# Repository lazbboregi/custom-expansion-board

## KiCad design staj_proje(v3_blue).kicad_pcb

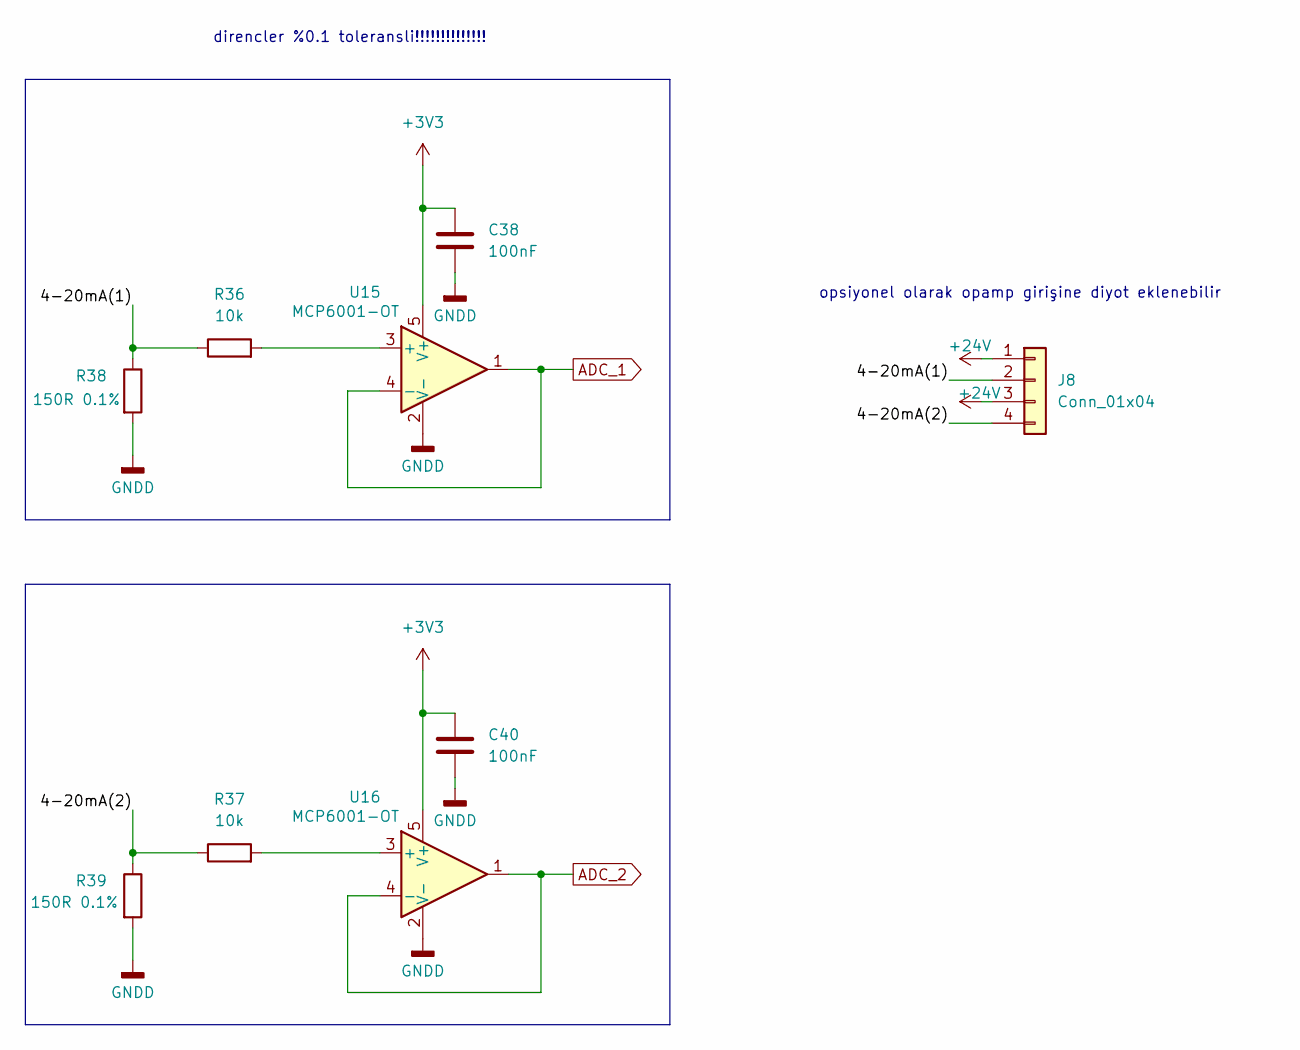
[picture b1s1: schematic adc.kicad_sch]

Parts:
C38, C40: 100nF; C_0805_2012Metric
J8: Conn_01x04; PhoenixContact_MC_1,5_4-G-3.81_1x04_P3.81mm_Horizontal
R36, R37: 10k; R_0805_2012Metric
R38, R39: 150R 0.1%; R_0805_2012Metric
U15, U16: MCP6001-OT; SOT-23-5

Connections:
+3V3: C38.1, C40.1, U15.5 (V+), U16.5 (V+); also elsewhere on the board
+24V: J8.1, J8.3; also elsewhere on the board
/ADC/4-20mA(1): J8.2, R36.1, R38.1
/ADC/4-20mA(2): J8.4, R37.1, R39.1
ADC_1: U15.1, U15.4 (-); also elsewhere on the board
ADC_2: U16.1, U16.4 (-); also elsewhere on the board
GNDD: C38.2, C40.2, R38.2, R39.2, U15.2 (V-), U16.2 (V-); also elsewhere on the board
unnamed: R36.2, U15.3 (+)
unnamed: R37.2, U16.3 (+)

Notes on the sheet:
direncler %0.1 toleransli!!!!!!!!!!!!!!
opsiyonel olarak opamp girişine diyot eklenebilir

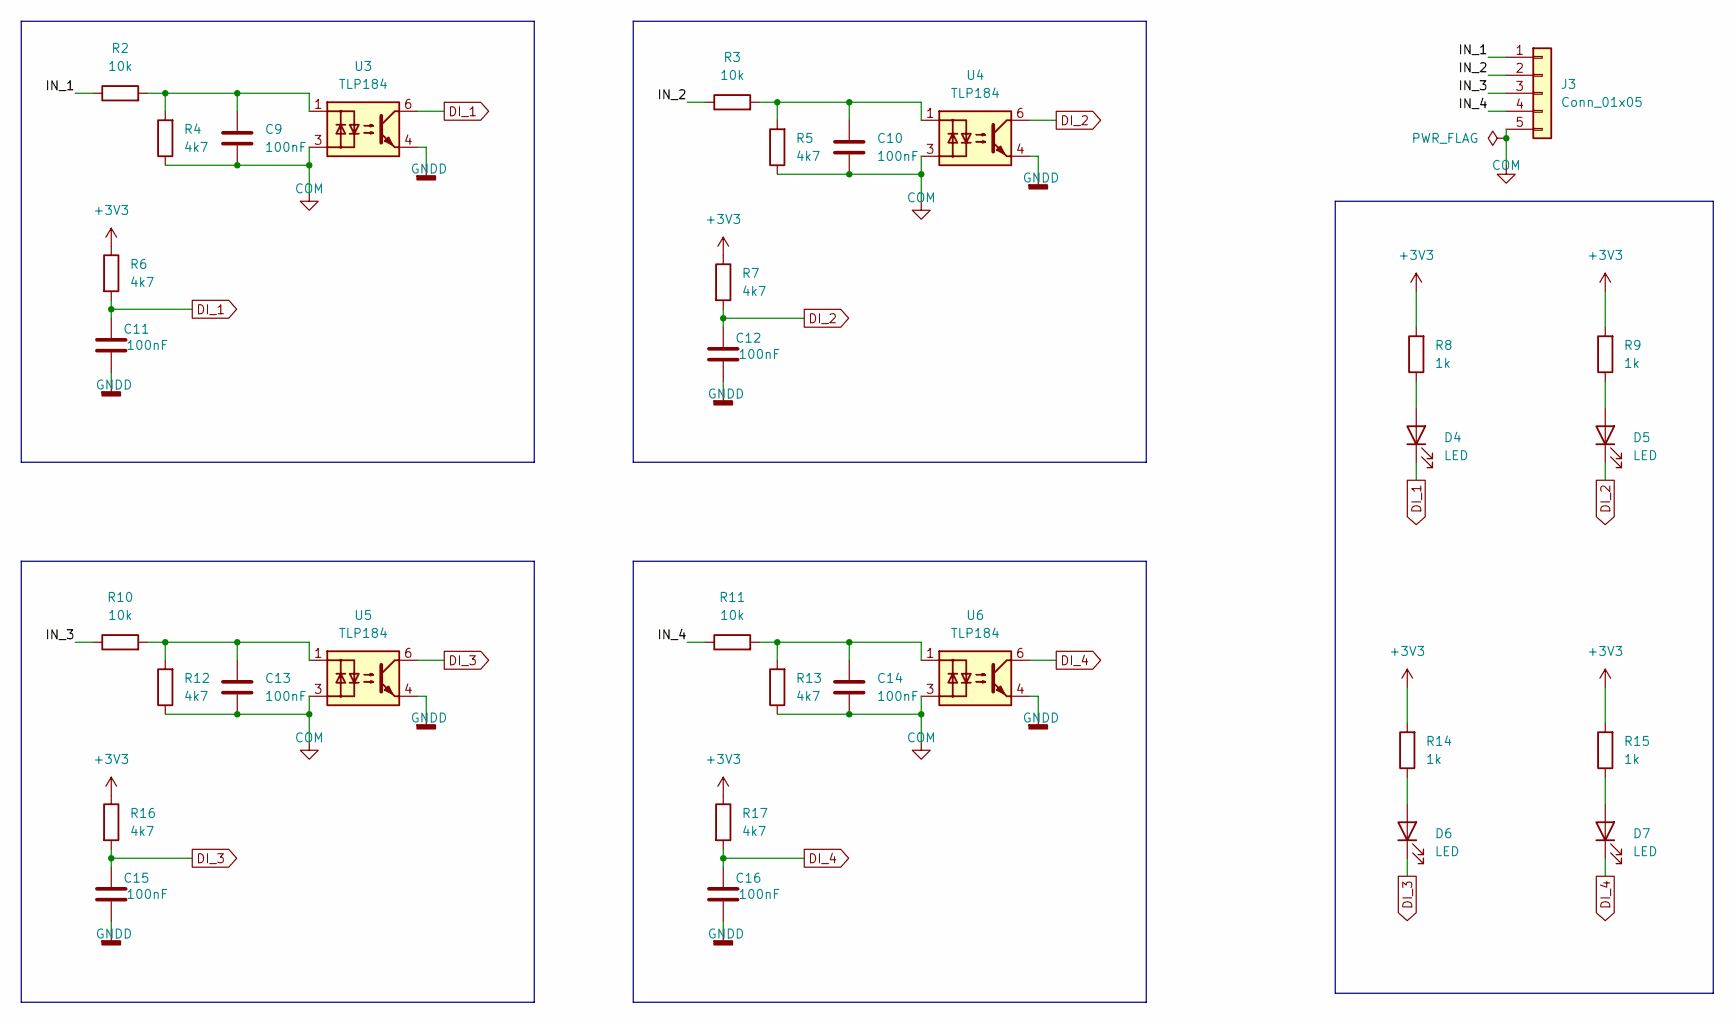
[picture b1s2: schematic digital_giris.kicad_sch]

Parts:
C9, C10, C11, C12, C13, C14, C15, C16: 100nF; C_0805_2012Metric
D4, D5, D6, D7: LED; LED_0603_1608Metric
J3: Conn_01x05; PhoenixContact_MC_1,5_5-G-3.81_1x05_P3.81mm_Horizontal
R2, R3, R10, R11: 10k; R_0805_2012Metric
R4, R5, R6, R7, R12, R13, R16, R17: 4k7; R_0805_2012Metric
R8, R9, R14, R15: 1k; R_0805_2012Metric
U3, U4, U5, U6: TLP184; Toshiba_SOIC-4-6_4.4x3.6mm_P1.27mm

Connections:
+3V3: R6.1, R7.1, R8.2, R9.2, R14.2, R15.2, R16.1, R17.1; also elsewhere on the board
/4x izole digital giris/IN_1: J3.1, R2.1
/4x izole digital giris/IN_2: J3.2, R3.1
/4x izole digital giris/IN_3: J3.3, R10.1
/4x izole digital giris/IN_4: J3.4, R11.1
COM: C9.1, C10.1, C13.1, C14.1, J3.5, R4.1, R5.1, R12.1, R13.1, U3.3, U4.3, U5.3, U6.3
DI_1: C11.1, D4.1 (K), R6.2, U3.6; also elsewhere on the board
DI_2: C12.1, D5.1 (K), R7.2, U4.6; also elsewhere on the board
DI_3: C15.1, D6.1 (K), R16.2, U5.6; also elsewhere on the board
DI_4: C16.1, D7.1 (K), R17.2, U6.6; also elsewhere on the board
GNDD: C11.2, C12.2, C15.2, C16.2, U3.4, U4.4, U5.4, U6.4; also elsewhere on the board
unnamed: C9.2, R2.2, R4.2, U3.1
unnamed: C10.2, R3.2, R5.2, U4.1
unnamed: C13.2, R10.2, R12.2, U5.1
unnamed: C14.2, R11.2, R13.2, U6.1
unnamed: D4.2 (A), R8.1
unnamed: D5.2 (A), R9.1
unnamed: D6.2 (A), R14.1
unnamed: D7.2 (A), R15.1

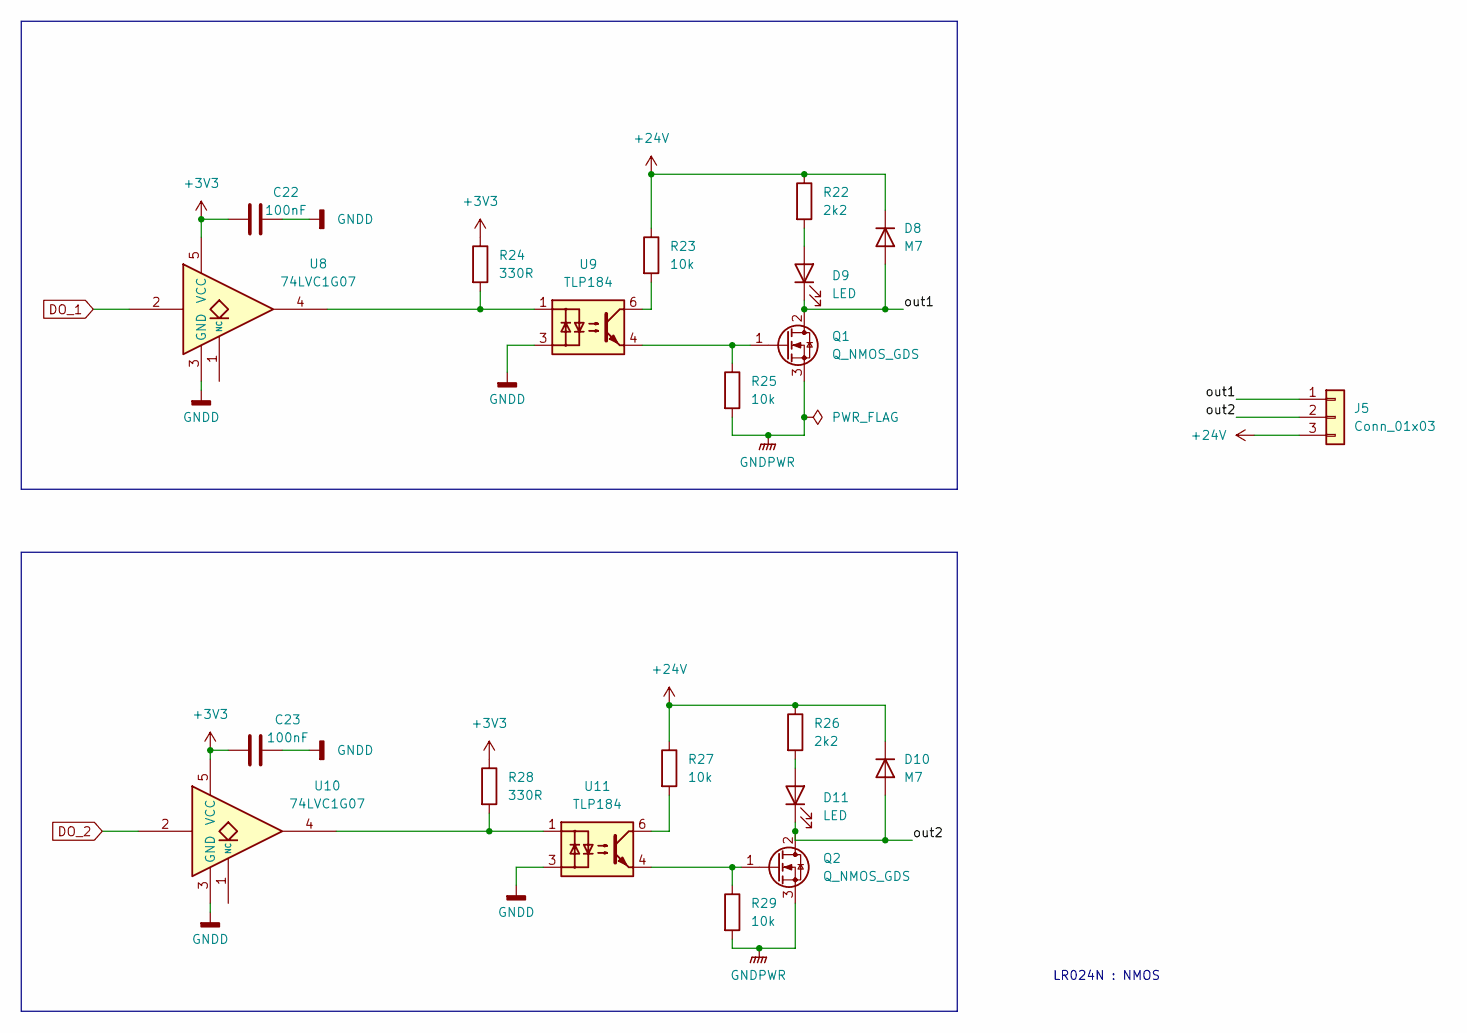
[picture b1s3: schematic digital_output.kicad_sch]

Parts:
C22, C23: 100nF; C_0805_2012Metric
D8, D10: M7; D_SMA
D9, D11: LED; LED_0603_1608Metric
J5: Conn_01x03; PhoenixContact_MC_1,5_3-G-3.81_1x03_P3.81mm_Horizontal
Q1, Q2: Q_NMOS_GDS; TO-252-3_TabPin2
R22, R26: 2k2; R_0805_2012Metric
R23, R25, R27, R29: 10k; R_0805_2012Metric
R24, R28: 330R; R_0805_2012Metric
U8, U10: 74LVC1G07; SOT-23-5
U9, U11: TLP184; Toshiba_SOIC-4-6_4.4x3.6mm_P1.27mm

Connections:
+3V3: C22.2, C23.2, R24.1, R28.1, U8.5 (VCC), U10.5 (VCC); also elsewhere on the board
+24V: D8.1 (K), D10.1 (K), J5.3, R22.1, R23.1, R26.1, R27.1; also elsewhere on the board
/2x digital output/out1: D8.2 (A), D9.1 (K), J5.1, Q1.2 (D)
/2x digital output/out2: D10.2 (A), D11.1 (K), J5.2, Q2.2 (D)
DO_1: U8.2; also elsewhere on the board
DO_2: U10.2; also elsewhere on the board
GNDD: C22.1, C23.1, U8.3 (GND), U9.3, U10.3 (GND), U11.3; also elsewhere on the board
GNDPWR: Q1.3 (S), Q2.3 (S), R25.2, R29.2
unnamed: D9.2 (A), R22.2
unnamed: D11.2 (A), R26.2
unnamed: Q1.1 (G), R25.1, U9.4
unnamed: Q2.1 (G), R29.1, U11.4
unnamed: R23.2, U9.6
unnamed: R24.2, U8.4, U9.1
unnamed: R27.2, U11.6
unnamed: R28.2, U10.4, U11.1

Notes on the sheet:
LR024N : NMOS

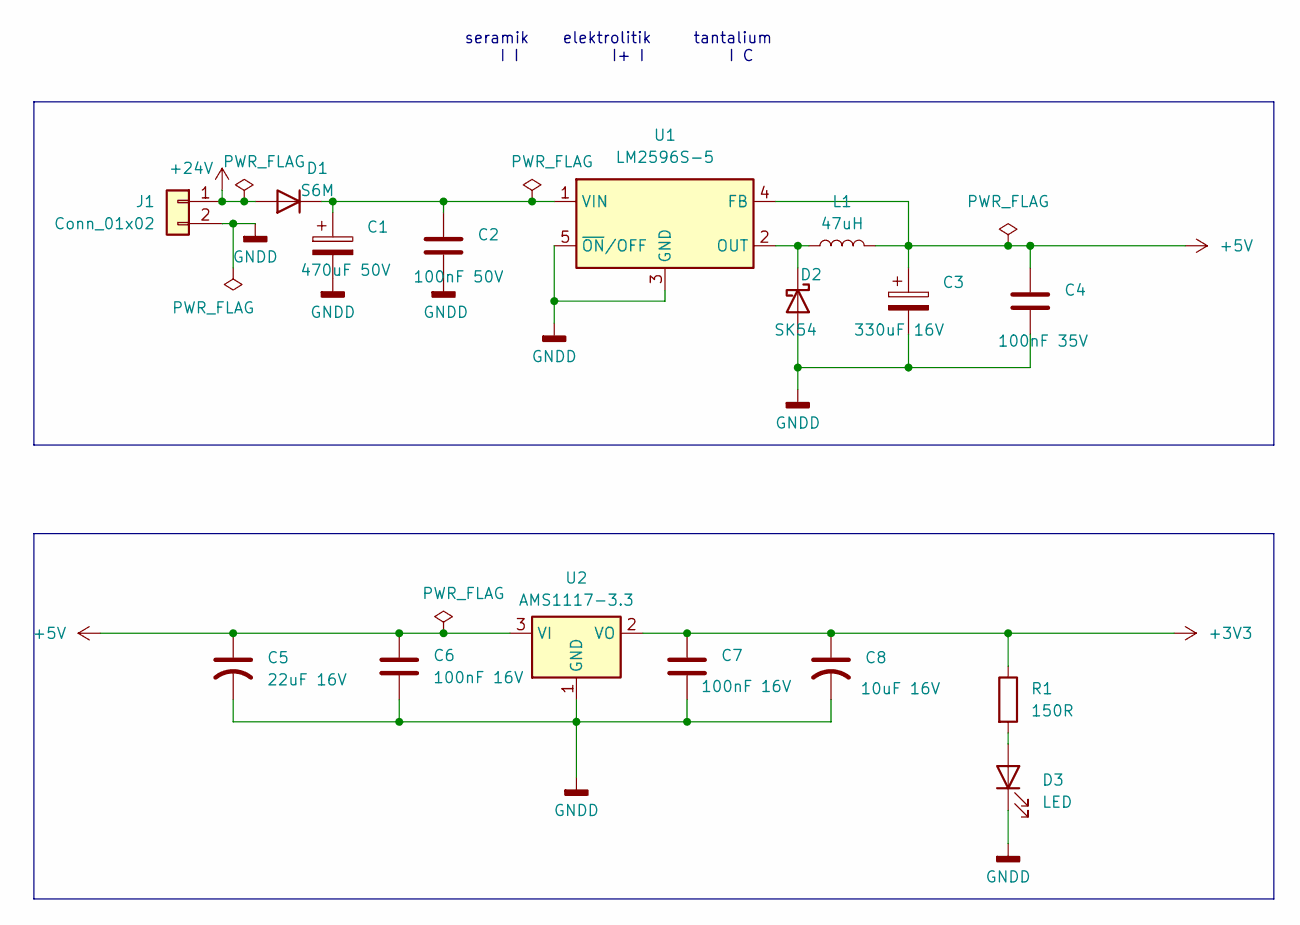
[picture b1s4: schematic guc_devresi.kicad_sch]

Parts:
C1: 470uF 50V; CP_Elec_8x10
C2: 100nF 50V; C_0805_2012Metric
C3: 330uF 16V; CP_Elec_8x10
C4: 100nF 35V; C_0805_2012Metric
C5: 22uF 16V; CP_EIA-3528-21_Kemet-B
C6, C7: 100nF 16V; C_0805_2012Metric
C8: 10uF 16V; CP_EIA-3528-21_Kemet-B
D1: S6M; D_SMC
D2: SK54; ST_D_SMC
D3: LED; LED_0603_1608Metric
J1: Conn_01x02; PhoenixContact_MC_1,5_2-G-3.81_1x02_P3.81mm_Horizontal
L1: 47uH; WE-PD_1210
R1: 150R; R_0805_2012Metric
U1: LM2596S-5; TO-263-5_TabPin3
U2: AMS1117-3.3; SOT-223-3_TabPin2

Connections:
+3V3: C7.1, C8.1, R1.1, U2.2 (VO); also elsewhere on the board
+5V: C3.1, C4.1, C5.1, C6.1, L1.2, U1.4 (FB), U2.3 (VI); also elsewhere on the board
+24V: D1.2 (A), J1.1; also elsewhere on the board
GNDD: C1.2, C2.2, C3.2, C4.2, C5.2, C6.2, C7.2, C8.2, D2.2 (A), D3.1 (K), J1.2, U1.3 (GND), U1.5 (~ON/OFF), U2.1 (GND); also elsewhere on the board
unnamed: C1.1, C2.1, D1.1 (K), U1.1 (VIN)
unnamed: D2.1 (K), L1.1, U1.2 (OUT)
unnamed: D3.2 (A), R1.2

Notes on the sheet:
seramik elektrolitik tantalium I I I+ I I C

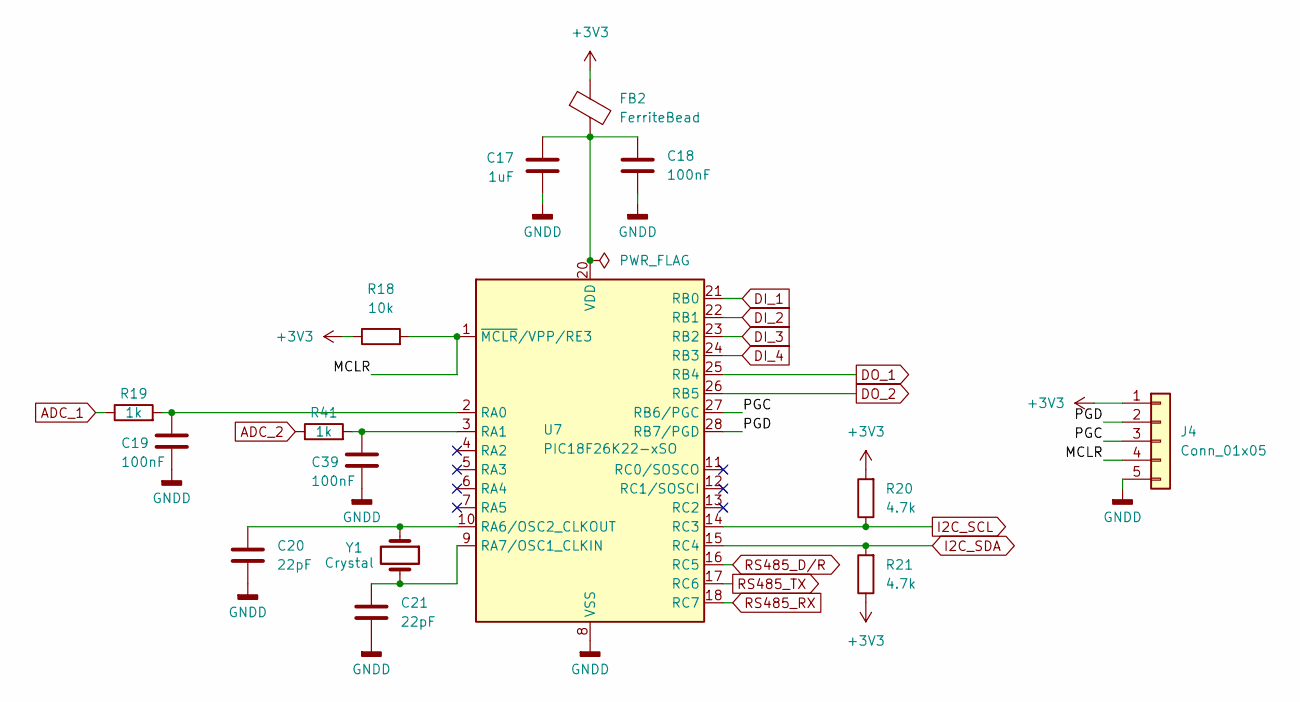
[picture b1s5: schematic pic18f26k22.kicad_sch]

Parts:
C17: 1uF; C_0805_2012Metric
C18, C19, C39: 100nF; C_0805_2012Metric
C20, C21: 22pF; C_0805_2012Metric
FB2: FerriteBead; L_0805_2012Metric
J4: Conn_01x05; PinHeader_1x05_P2.54mm_Vertical
R18: 10k; R_0805_2012Metric
R19, R41: 1k; R_0805_2012Metric
R20, R21: 4.7k; R_0805_2012Metric
U7: PIC18F26K22-xSO; SOIC-28W_7.5x17.9mm_P1.27mm
Y1: Crystal; Crystal_SMD_HC49-SD

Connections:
+3V3: FB2.1, J4.1, R18.1, R20.2, R21.1; also elsewhere on the board
/MCU/MCLR: J4.4, R18.2, U7.1 (~MCLR/VPP/RE3)
/MCU/PGC: J4.3, U7.27 (RB6/PGC)
/MCU/PGD: J4.2, U7.28 (RB7/PGD)
ADC_1: R19.1; also elsewhere on the board
ADC_2: R41.1; also elsewhere on the board
DI_1: U7.21 (RB0); also elsewhere on the board
DI_2: U7.22 (RB1); also elsewhere on the board
DI_3: U7.23 (RB2); also elsewhere on the board
DI_4: U7.24 (RB3); also elsewhere on the board
DO_1: U7.25 (RB4); also elsewhere on the board
DO_2: U7.26 (RB5); also elsewhere on the board
GNDD: C17.1, C18.2, C19.2, C20.2, C21.2, C39.2, J4.5, U7.8 (VSS), U7.19 (VSS); also elsewhere on the board
I2C_SCL: R20.1, U7.14 (RC3); also elsewhere on the board
I2C_SDA: R21.2, U7.15 (RC4); also elsewhere on the board
unnamed: C19.1, R19.2, U7.2 (RA0)
unnamed: C39.1, R41.2, U7.3 (RA1)
unnamed: C20.1, U7.10 (RA6/OSC2_CLKOUT), Y1.1
unnamed: C21.1, U7.9 (RA7/OSC1_CLKIN), Y1.2
unnamed: C17.2, C18.1, FB2.2, U7.20 (VDD)
RS485_D/R: U7.16 (RC5); also elsewhere on the board
RS485_RX: U7.18 (RC7); also elsewhere on the board
RS485_TX: U7.17 (RC6); also elsewhere on the board

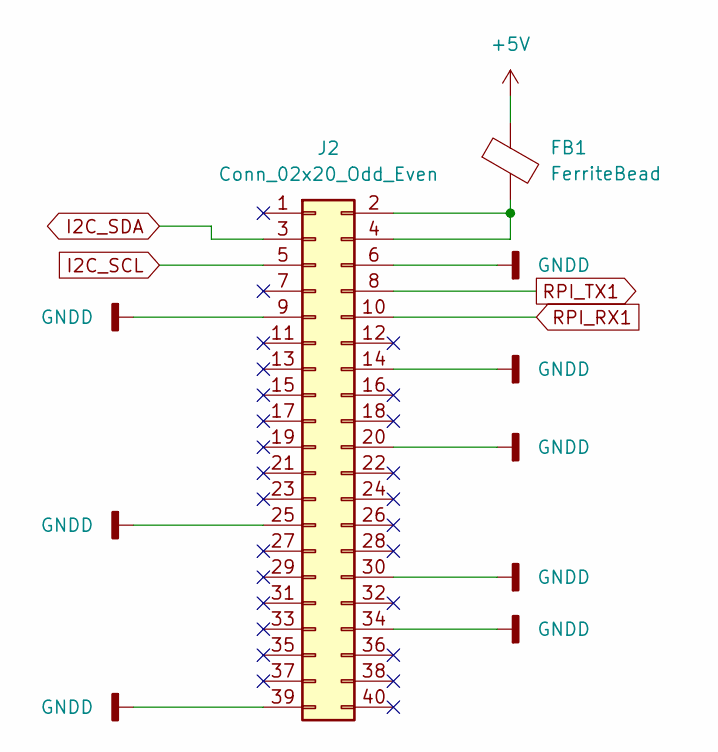
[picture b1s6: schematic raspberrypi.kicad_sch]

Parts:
FB1: FerriteBead; L_0805_2012Metric
J2: Conn_02x20_Odd_Even; RaspberryPİ4

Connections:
+5V: FB1.1; also elsewhere on the board
GNDD: J2.6, J2.9, J2.14, J2.20, J2.25, J2.30, J2.34, J2.39; also elsewhere on the board
I2C_SCL: J2.5; also elsewhere on the board
I2C_SDA: J2.3; also elsewhere on the board
unnamed: FB1.2, J2.2, J2.4
RPI_RX1: J2.10; also elsewhere on the board
RPI_TX1: J2.8; also elsewhere on the board

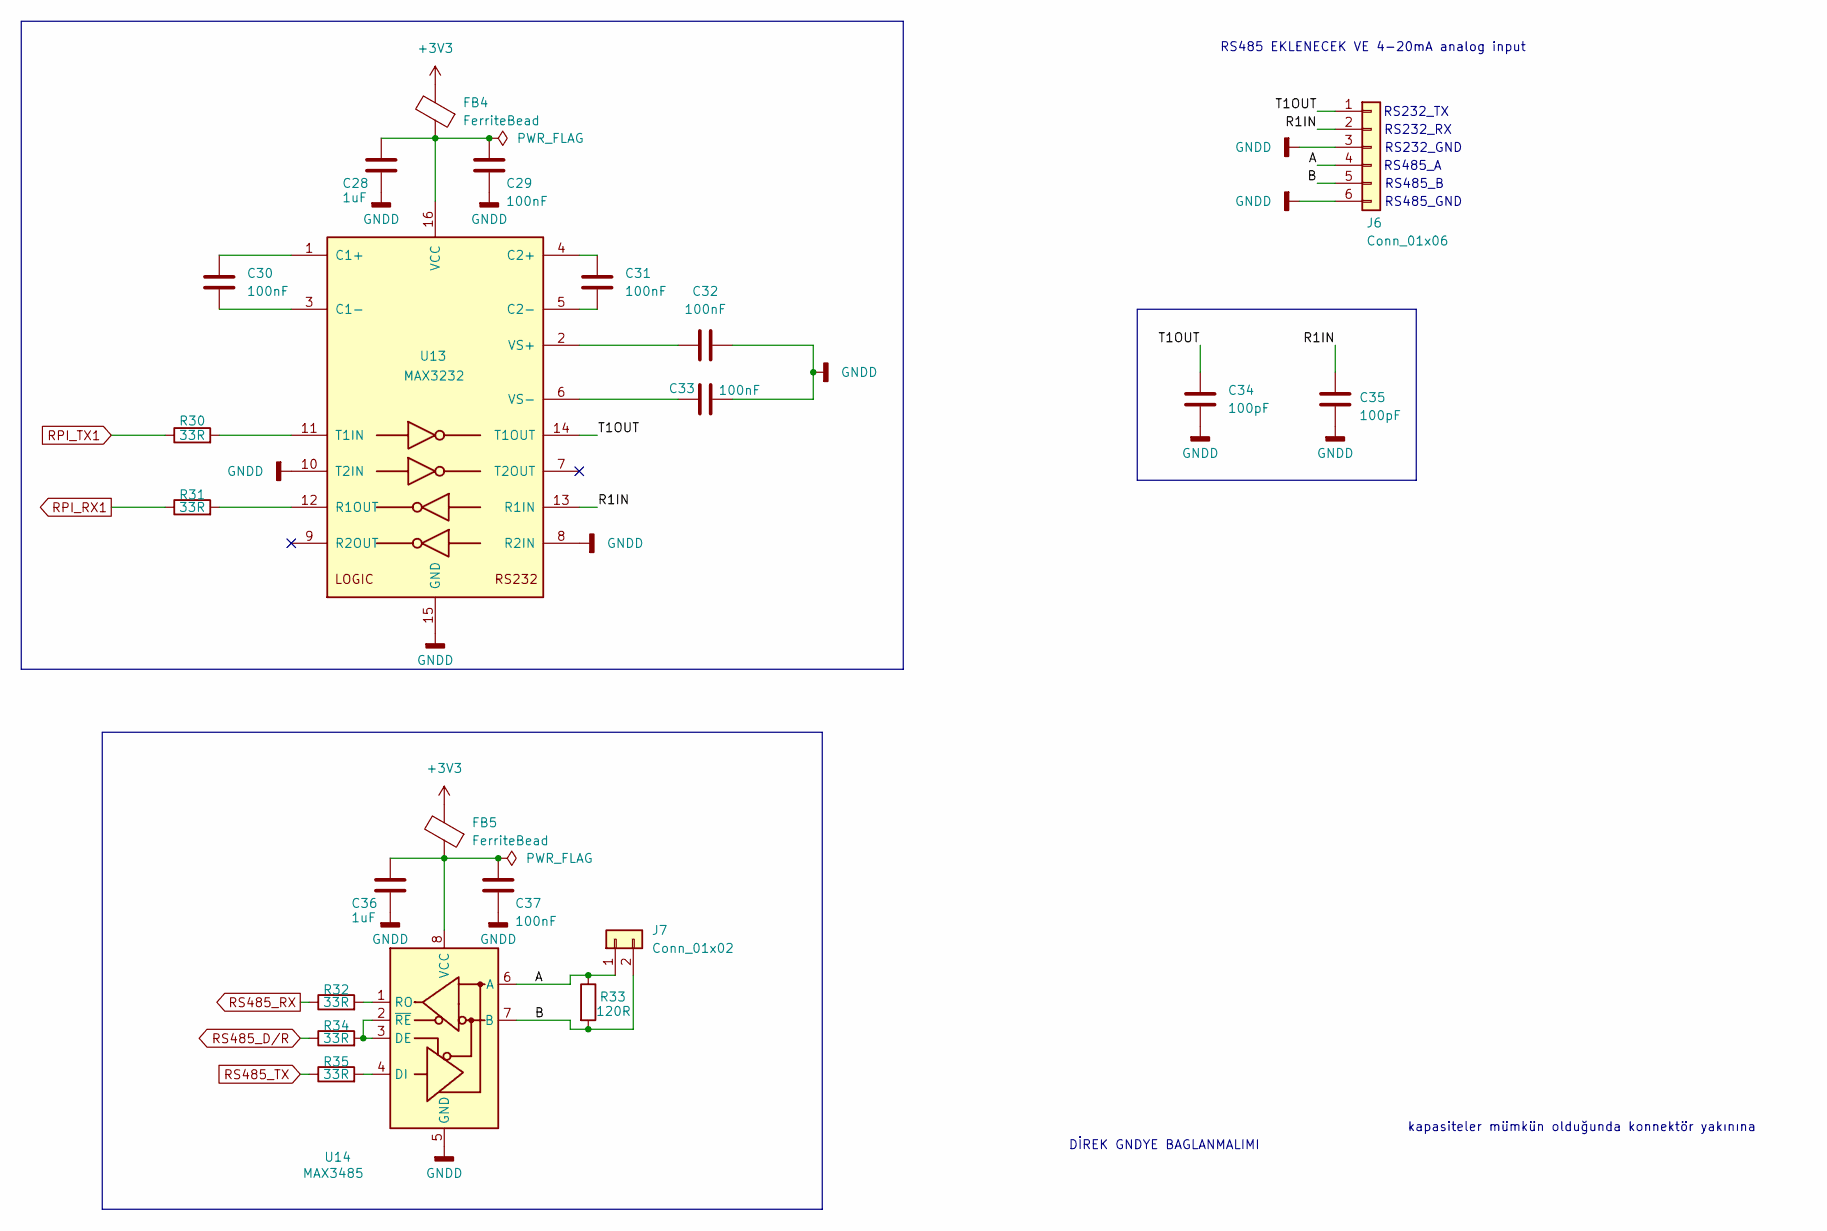
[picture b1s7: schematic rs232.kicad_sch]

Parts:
C28, C36: 1uF; C_0805_2012Metric
C29, C30, C31, C32, C33, C37: 100nF; C_0805_2012Metric
C34, C35: 100pF; C_0805_2012Metric
FB4, FB5: FerriteBead; L_0805_2012Metric
J6: Conn_01x06; PhoenixContact_MC_1,5_6-G-3.81_1x06_P3.81mm_Horizontal
J7: Conn_01x02; PinHeader_1x02_P2.54mm_Vertical
R30, R31, R32, R34, R35: 33R; R_0805_2012Metric
R33: 120R; R_0805_2012Metric
U13: MAX3232; SOIC-16_3.9x9.9mm_P1.27mm
U14: MAX3485; SOIC-8_3.9x4.9mm_P1.27mm

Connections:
+3V3: FB4.2, FB5.2; also elsewhere on the board
/rs232 COM portu/A: J6.4, J7.1, R33.1, U14.6 (A)
/rs232 COM portu/B: J6.5, J7.2, R33.2, U14.7 (B)
/rs232 COM portu/R1IN: C35.1, J6.2, U13.13 (R1IN)
/rs232 COM portu/T1OUT: C34.1, J6.1, U13.14 (T1OUT)
GNDD: C28.1, C29.2, C32.2, C33.2, C34.2, C35.2, C36.1, C37.2, J6.3, J6.6, U13.8 (R2IN), U13.10 (T2IN), U13.15 (GND), U14.5 (GND); also elsewhere on the board
unnamed: C30.1, U13.1 (C1+)
unnamed: C30.2, U13.3 (C1-)
unnamed: C31.1, U13.4 (C2+)
unnamed: C31.2, U13.5 (C2-)
unnamed: R31.2, U13.12 (R1OUT)
unnamed: R30.2, U13.11 (T1IN)
unnamed: C28.2, C29.1, FB4.1, U13.16 (VCC)
unnamed: C32.1, U13.2 (VS+)
unnamed: C33.1, U13.6 (VS-)
unnamed: R34.2, U14.2 (~RE), U14.3 (DE)
unnamed: R35.2, U14.4 (DI)
unnamed: R32.2, U14.1 (RO)
unnamed: C36.2, C37.1, FB5.1, U14.8 (VCC)
RPI_RX1: R31.1; also elsewhere on the board
RPI_TX1: R30.1; also elsewhere on the board
RS485_D/R: R34.1; also elsewhere on the board
RS485_RX: R32.1; also elsewhere on the board
RS485_TX: R35.1; also elsewhere on the board

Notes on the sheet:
RS485_B
DİREK GNDYE BAGLANMALIMI
RS485_A
kapasiteler mümkün olduğunda konnektör yakınına
RS232_GND
RS232_RX
RS232_TX
RS485_GND
RS485 EKLENECEK VE 4-20mA analog input

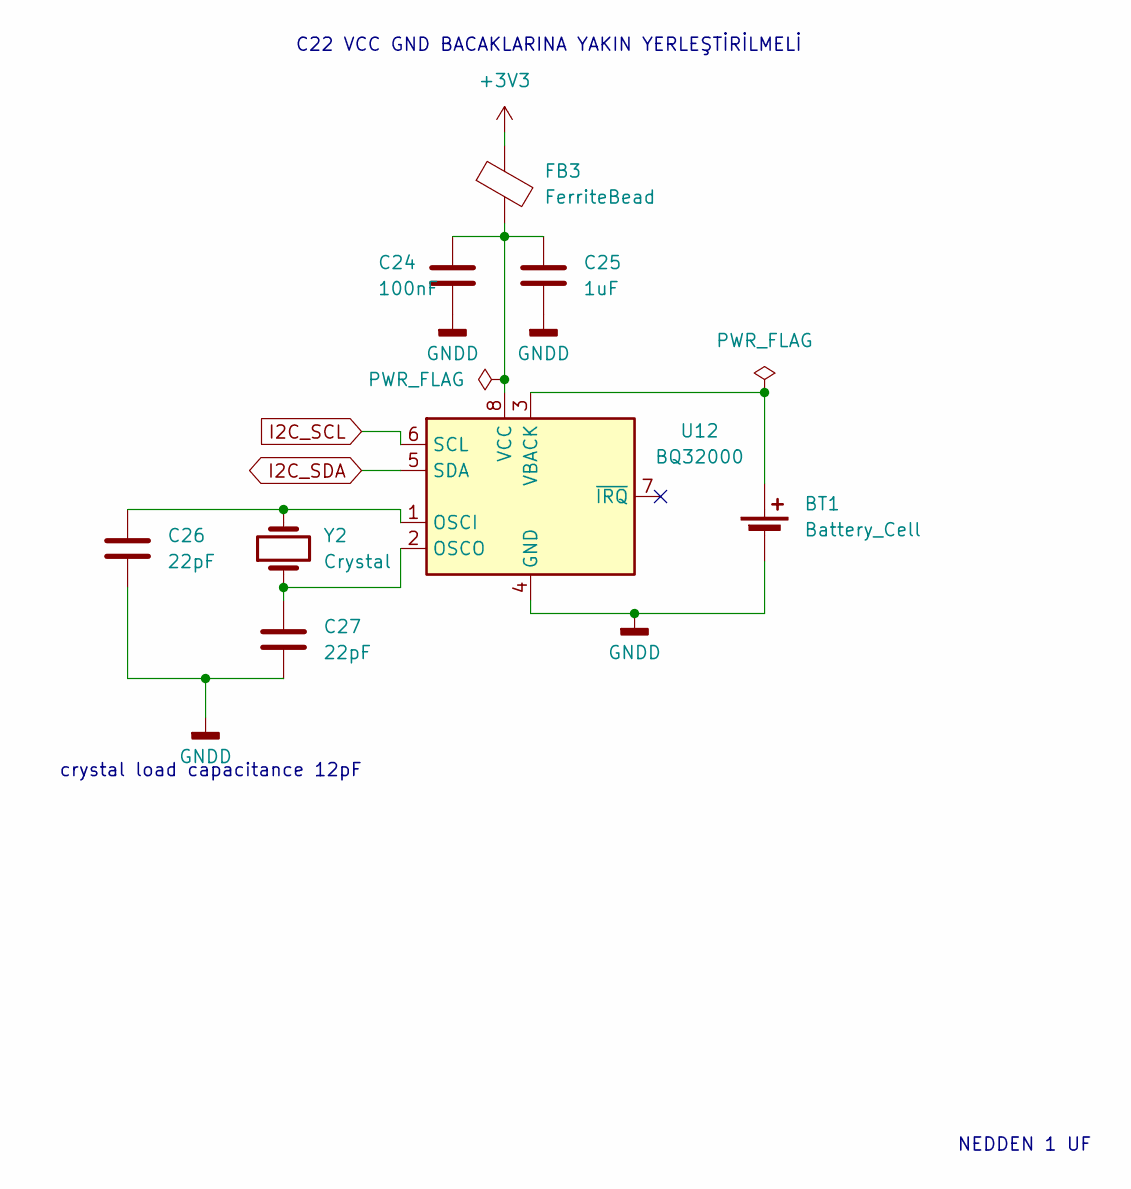
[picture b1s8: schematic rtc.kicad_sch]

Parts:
BT1: Battery_Cell; BatteryHolder_CR2032
C24: 100nF; C_0805_2012Metric
C25: 1uF; C_0805_2012Metric
C26, C27: 22pF; C_0805_2012Metric
FB3: FerriteBead; L_0805_2012Metric
U12: BQ32000; SOIC-8_3.9x4.9mm_P1.27mm
Y2: Crystal; Crystal_Round_D3.0mm_Vertical

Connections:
+3V3: FB3.1; also elsewhere on the board
GNDD: BT1.2 (-), C24.2, C25.1, C26.1, C27.1, U12.4 (GND); also elsewhere on the board
I2C_SCL: U12.6 (SCL); also elsewhere on the board
I2C_SDA: U12.5 (SDA); also elsewhere on the board
unnamed: BT1.1 (+), U12.3 (VBACK)
unnamed: C26.2, U12.1 (OSCI), Y2.2
unnamed: C27.2, U12.2 (OSCO), Y2.1
unnamed: C24.1, C25.2, FB3.2, U12.8 (VCC)

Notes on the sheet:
crystal load capacitance 12pF
C22 VCC GND BACAKLARINA YAKIN YERLEŞTİRİLMELİ
NEDDEN 1 UF

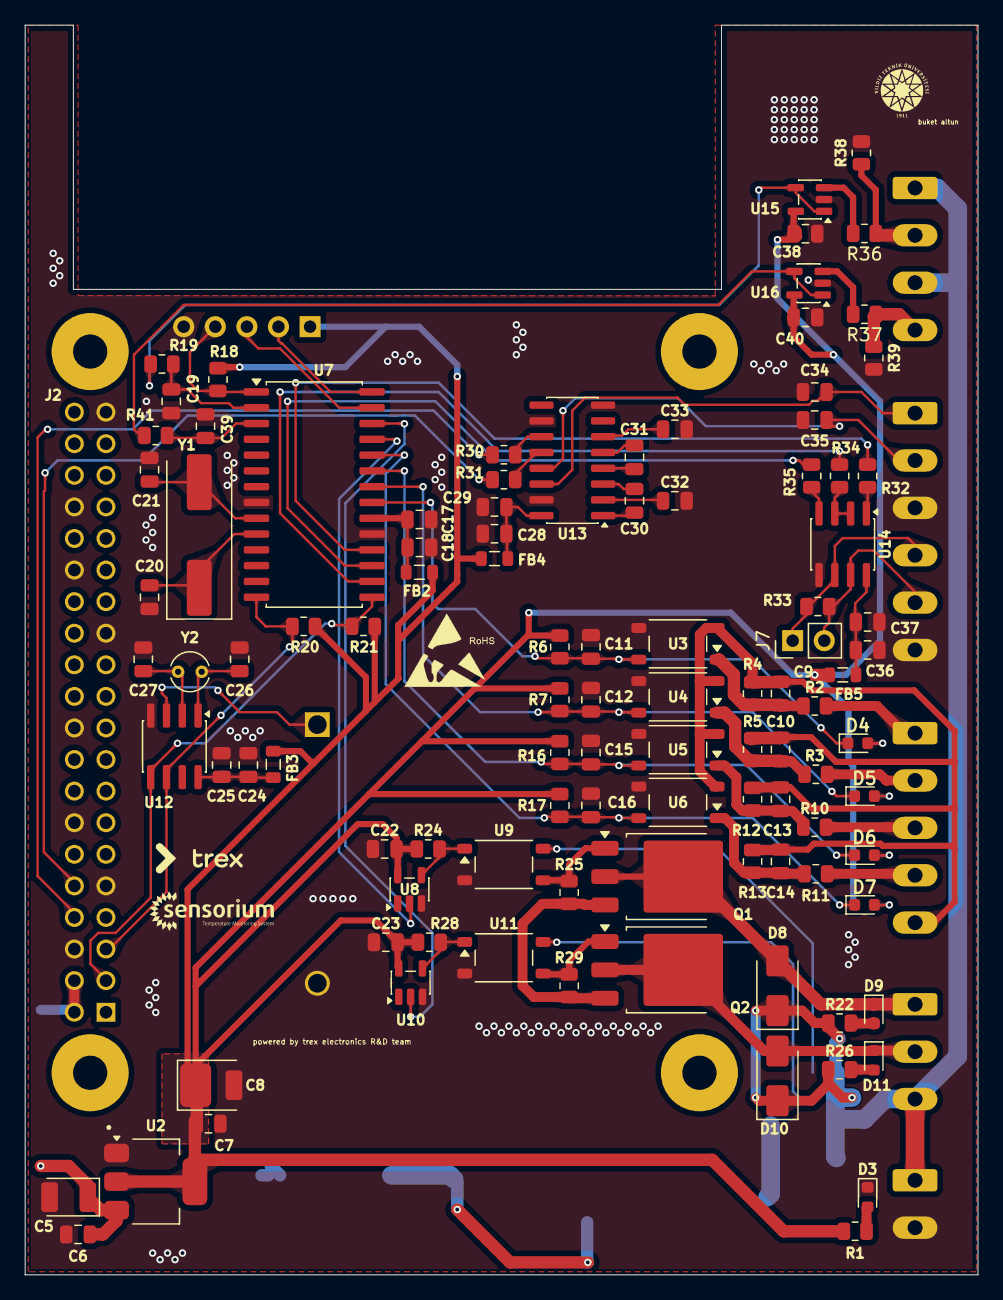
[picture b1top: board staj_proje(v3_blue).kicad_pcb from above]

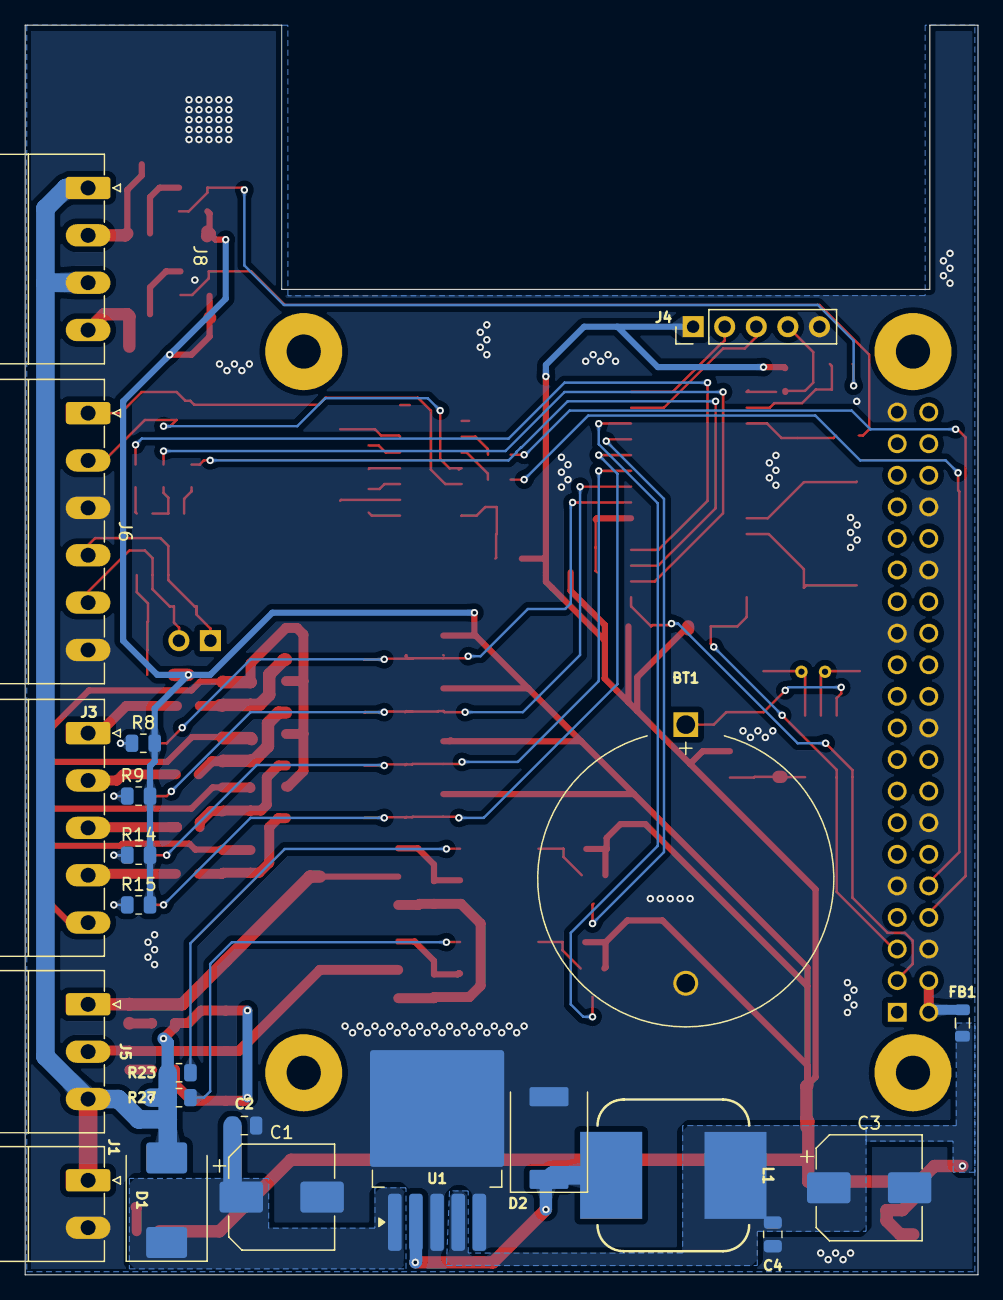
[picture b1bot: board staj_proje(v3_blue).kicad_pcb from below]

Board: 2 copper layers, 76.6 x 100.5 mm, 126 parts (22 on the bottom side), 80 nets.
